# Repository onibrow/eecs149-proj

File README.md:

# EECS149/249A Final Project - Bop It! Rhythm Game

Sanga Park, Seiya Ono, Ryan Tsang, Jehan Yang

[Video](https://www.youtube.com/watch?v=G22i39vs388&feature=youtu.be)

------
Setting up a lab computer:

```bash
cd ~/buckler/software
git clone https://github.com/onibrow/eecs149-proj
cd eecs149-proj
./setup_vm
```

## Proposal (10/25)

[Spreadsheet](https://docs.google.com/spreadsheets/d/1WutyDuHFwCbV_97uEuxx-2Y0jQ0Z9K7RMsq6U2ZCgrc/edit?usp=sharing)

**Project Goal**

We will implement a discrete note, single dimension rhythm game similar to Guitar Hero where the player is required to, on beat, actuate inputs from a pool of predefined discrete buttons. We will take this style of gameplay and translate into a Bop It driven hardware and LED display for the beat map.

**Project Approach**

The gameplay with be modeled as a state machine that keeps track of the state of the game (in game play, idling, song selection, etc). The sensor inputs will generate interrupts that trigger different events within the game. Timing and synchronicity will be very important to make sure the LEDs are lighting up on cue with the music. As a final product, we would like to seamlessly take input from the player and translate that to well timed gameplay with LED signals and music.

## Getting out of dependency hell

1. Try to compile. What library is it missing? ex: `blah.h`
1. Does the file exist in the sdk? Find it by going to the sdk folder `~/buckler/software/nrf52x-base/sdk/nrf5_sdk_15.3.0` and running `find . -name 'blah.*'`. Take note of the directory the header and C file are located in.
1. Edit `eecs149-proj/vm_setup/Includes.mk`. You will need to add **2 Lines**:
    1. Near line 180, the `SDK_HEADER_PATHS` should end and become `SDK_SOURCE_PATHS`. Add a new line at the end of the header paths and add the directory you found in step 2 for the header file. You might want to check if that directory is being checked already. ex: `SDK_HEADER_PATHS += $(SDK_ROOT)external/components/`
    1. Near line 270, the `SDK_SOURCE_PATHS` should end and is followed by `ifdef SERIALIZATiON_MODE`. Add a new line at the end of the source paths and add the directory you found in step 2 for the C file. Similarly, you might want to check if that directory is already being sourced. ex: `SDK_SOURCE_PATHS += $(SDK_ROOT)external/components/`
1. Edit `eecs149-proj/vm_setup/Board.mk`. You will need to add **1 Line**:
    1. Near line 95, the list of `BOARD_SOURCES` should end. Add the C file at the end of the list (make sure to terminate with a `\`). ex: `blah.c\`
1. Repeat the above steps for all dependencies.

## Notes
Meeting
MP3 files are compressed so they need to be decoded to be played on a DAC -> this isn't particularly ideal so we will switch over to WAV files which are uncompressed. From Audacity, we can see that we can save them in various formats (16 bit or 24 bit PCM), which will allow us to basically read in binary and shove them into either the I2S registers or over I2C. [Here](https://www.sparkfun.com/tutorials/160)'s a tutorial on how to play WAV files and goes over their limitations. 

## Useful Links:

[nRF52 Product Spec](https://infocenter.nordicsemi.com/pdf/nRF52832_PS_v1.4.pdf)

* I2S begins page 445
* [Loopback example for sanity check](https://infocenter.nordicsemi.com/index.jsp?topic=%2Fcom.nordic.infocenter.sdk5.v15.2.0%2Fi2s_example_loopback.html&cp=4_0_0_4_5_14)
* [nRF SDK I2S](https://infocenter.nordicsemi.com/topic/com.nordic.infocenter.sdk5.v15.3.0/group__nrfx__i2s.html)
* [MCP4725 DAC Driver](https://infocenter.nordicsemi.com/topic/com.nordic.infocenter.sdk5.v15.3.0/group__mcp4725.html)

[Nordic SD Card](https://infocenter.nordicsemi.com/topic/com.nordic.infocenter.sdk5.v15.3.0/app_sdcard_example.html)

[Nordic Timers](https://infocenter.nordicsemi.com/index.jsp?topic=%2Fcom.nordic.infocenter.sdk5.v15.3.0%2Fgroup__app__timer.html)

[SparkFun's Intro to SPI](https://learn.sparkfun.com/tutorials/serial-peripheral-interface-spi/all)

[RPi WS2801 SPI Interface](https://tutorials-raspberrypi.com/how-to-control-a-raspberry-pi-ws2801-rgb-led-strip/)

[WS2801 Datasheet](https://cdn-shop.adafruit.com/datasheets/WS2801.pdf)

[Adafruit WS2801 RPi SPI Library](https://github.com/adafruit/Adafruit_CircuitPython_WS2801)

[Audio Python Syncing](https://github.com/scottlawsonbc/audio-reactive-led-strip)

[RPI GPIO Interrupt Handling](http://raspberrywebserver.com/gpio/using-interrupt-driven-gpio.html)

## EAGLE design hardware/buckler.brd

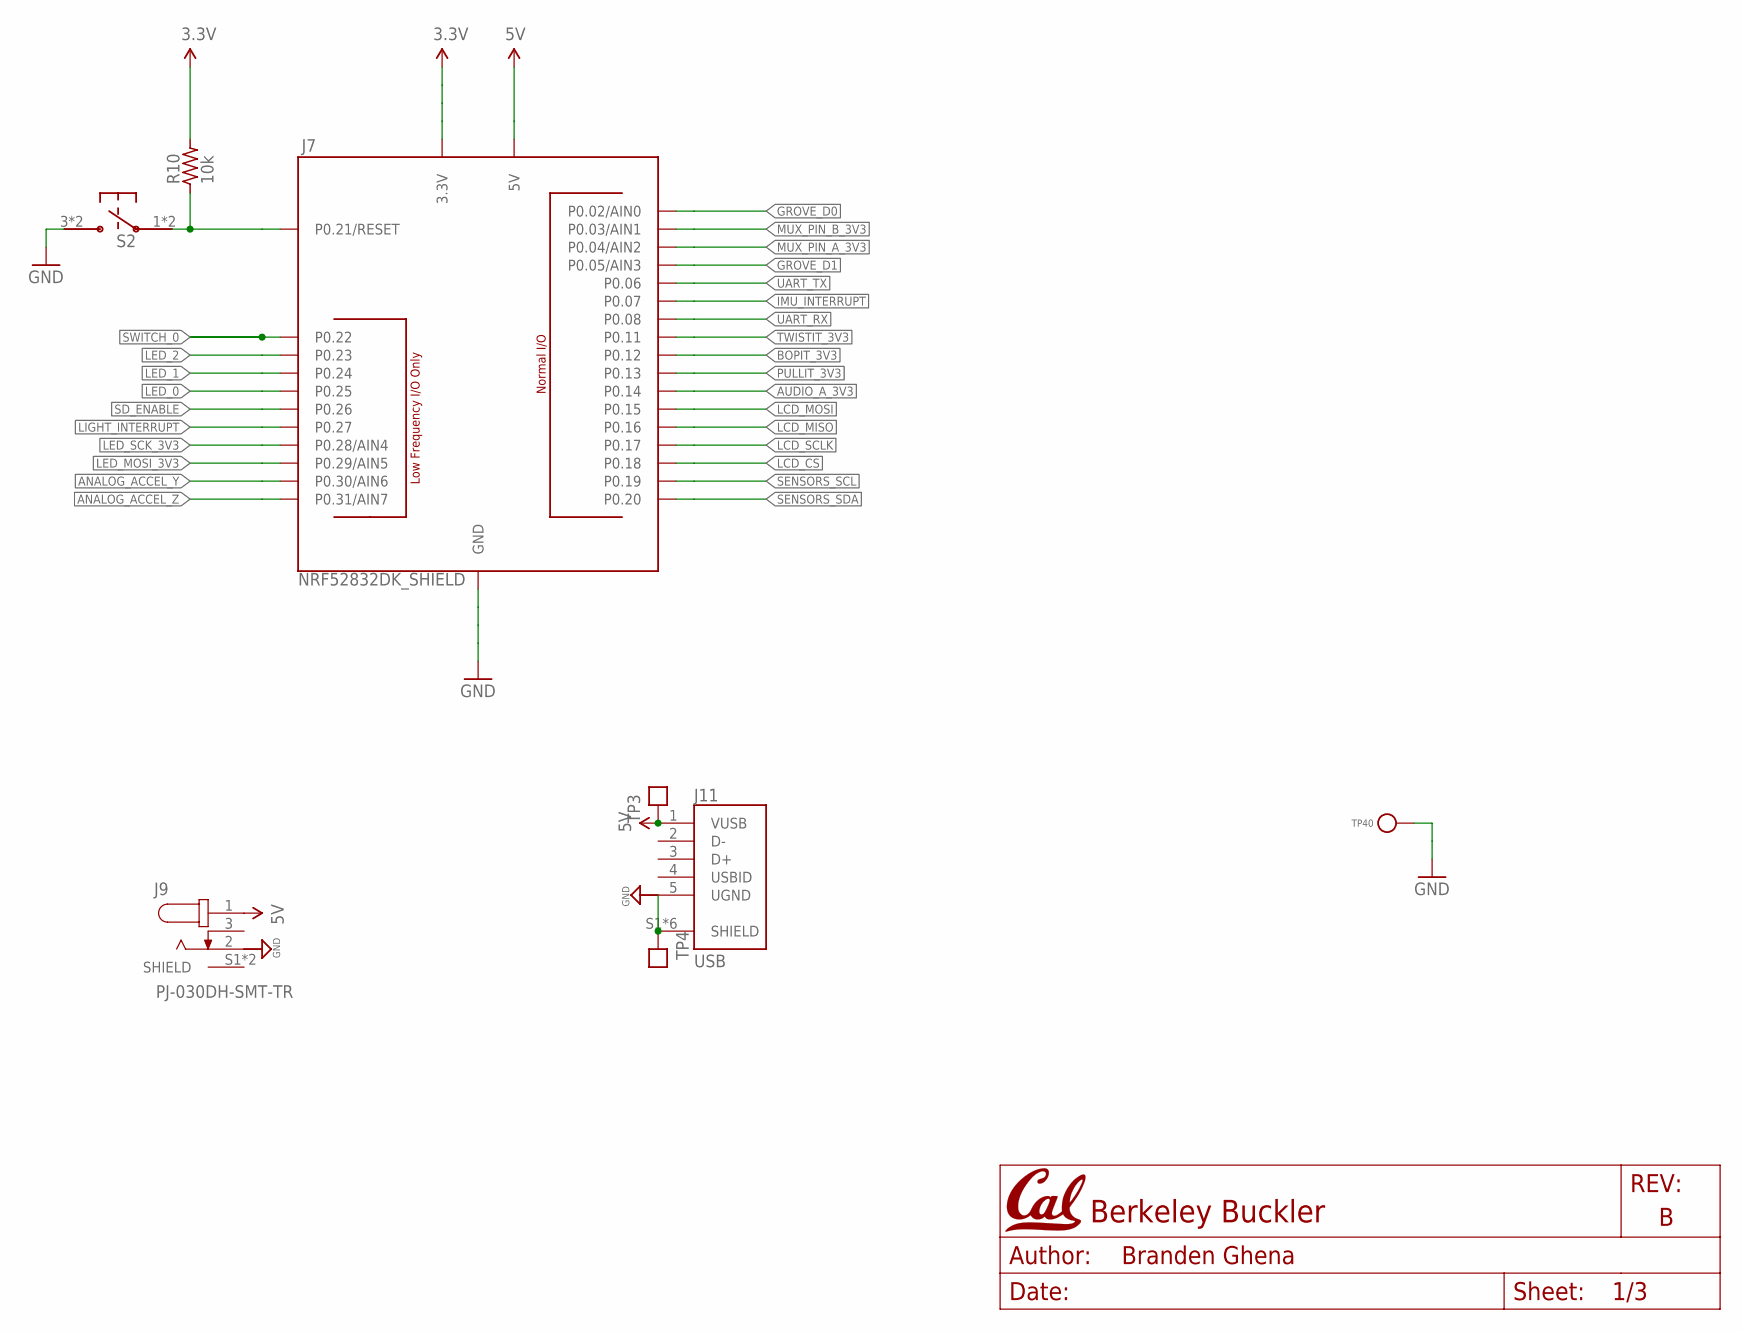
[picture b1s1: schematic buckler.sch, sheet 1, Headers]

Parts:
J7: NRF52832DK_SHIELD; DIGIKEY1 S1011EC-10-ND
J9: PJ-030DH-SMT-TR; CUI_PJ-030DH-SMT-TR
J11: USB; FCI_10103594-0001LF
R10: 10k; 0603-RES; MPN RC1005F103CS; DIGIKEY 1276-3431-1-ND
S2: PTS645SM43SMTR92; PTS645; MPN PTS645SM43SMTR92 LFS
TP3, TP4: TEST_POINTTHRU; TEST_POINT
TP40: TEST_POINT_0.078IN; TESTPOINT_0.078IN; MPN 1520-2; DIGIKEY 36-1520-2-ND

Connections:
3.3V: J7.3.3V@0 (3.3V), J7.3.3V@1 (3.3V), J7.3.3V@2 (3.3V), R10.2; also elsewhere on the board
5V: J7.5V, J9.1, J11.1 (VUSB), TP3.1; also elsewhere on the board
!IMU_INTERRUPT: J7.P0.07
!LCD_CS: J7.P0.18; also elsewhere on the board
!LED_0: J7.P0.25; also elsewhere on the board
!LED_1: J7.P0.24; also elsewhere on the board
!LED_2: J7.P0.23; also elsewhere on the board
!LIGHT_INTERRUPT: J7.P0.27
!RESET: J7.P0.21 (P0.21/RESET), R10.1, S2.1, S2.2
ANALOG_ACCEL_Y: J7.P0.30 (P0.30/AIN6)
ANALOG_ACCEL_Z: J7.P0.31 (P0.31/AIN7)
AUDIO_A_3V3: J7.P0.14; also elsewhere on the board
BOPIT_3V3: J7.P0.12; also elsewhere on the board
GND: J7.GND@0 (GND), J7.GND@1 (GND), J7.GND@2 (GND), J9.2, J11.5 (UGND), J11.S1 (SHIELD), J11.S2 (SHIELD), J11.S3 (SHIELD), J11.S4 (SHIELD), J11.S5 (SHIELD), J11.S6 (SHIELD), S2.3, S2.4, TP4.1, TP40.1; also elsewhere on the board
GROVE_D0: J7.P0.02 (P0.02/AIN0)
GROVE_D1: J7.P0.05 (P0.05/AIN3)
LCD_MISO: J7.P0.16; also elsewhere on the board
LCD_MOSI: J7.P0.15; also elsewhere on the board
LCD_SCLK: J7.P0.17; also elsewhere on the board
LED_MOSI_3V3: J7.P0.29 (P0.29/AIN5); also elsewhere on the board
LED_SCK_3V3: J7.P0.28 (P0.28/AIN4); also elsewhere on the board
MUX_PIN_A_3V3: J7.P0.04 (P0.04/AIN2); also elsewhere on the board
MUX_PIN_B_3V3: J7.P0.03 (P0.03/AIN1); also elsewhere on the board
PULLIT_3V3: J7.P0.13; also elsewhere on the board
SD_ENABLE: J7.P0.26
SENSORS_SCL: J7.P0.19
SENSORS_SDA: J7.P0.20
SWITCH_0: J7.P0.22
TWISTIT_3V3: J7.P0.11; also elsewhere on the board
UART_RX: J7.P0.08
UART_TX: J7.P0.06

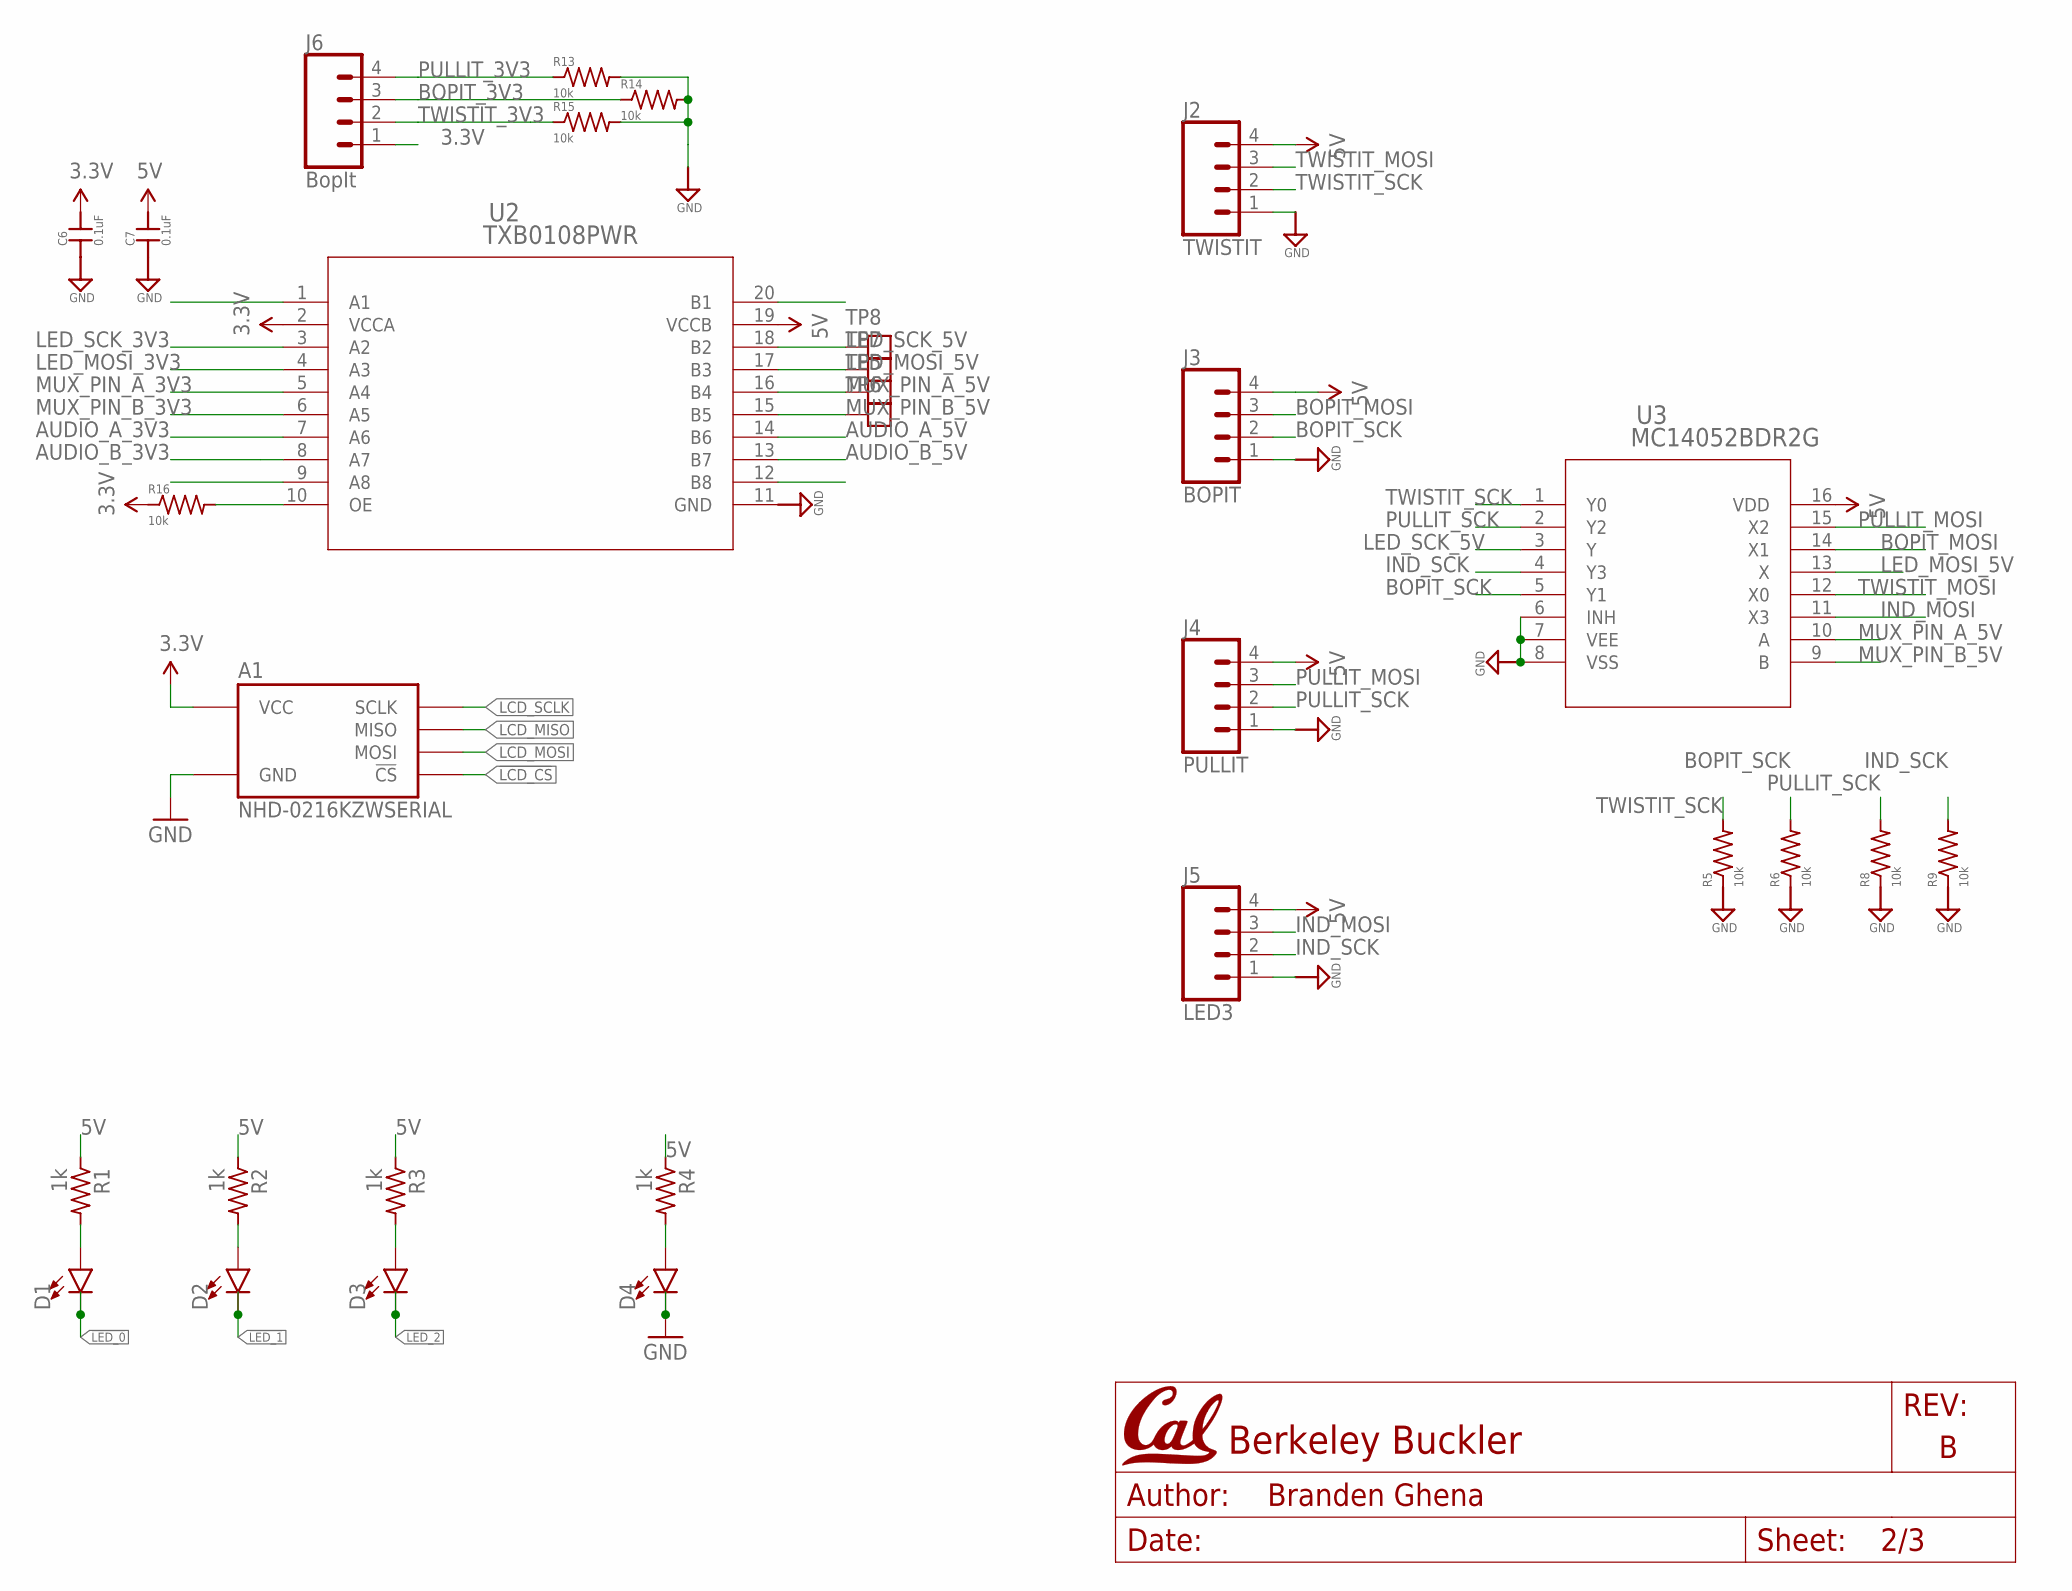
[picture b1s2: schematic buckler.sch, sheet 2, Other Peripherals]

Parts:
A1: NHD-0216KZWSERIAL; NHD-0216KZW; DIGIKEY1 NHD-0216KZW-AG5-ND
C6, C7: 0.1uF; 0603-CAP
D1, D2, D3, D4: LED0603; LED-0603
J2: TWISTIT; MOLEX-1X4
J3: BOPIT; MOLEX-1X4
J4: PULLIT; MOLEX-1X4
J5: LED3; MOLEX-1X4
J6: BopIt; MOLEX-1X4
R1, R2, R3, R4: 1k; 0603-RES; MPN RMCF0402FT1K00; DIGIKEY RMCF0402FT1K00CT-ND
R5, R6, R8, R9, R13, R14, R15, R16: 10k; 0603-RES
TP5, TP6, TP7, TP8: TEST_POINTTHRU; TEST_POINT
U2: TXB0108PWR; PW20
U3: MC14052BDR2G; SOIC-16

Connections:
3.3V: A1.2 (VCC), C6.2, J6.1, R16.1, U2.2 (VCCA); also elsewhere on the board
5V: C7.2, J2.4, J3.4, J4.4, J5.4, R1.1, R2.1, R3.1, R4.1, U2.19 (VCCB), U3.16 (VDD); also elsewhere on the board
!LCD_CS: A1.16 (!CS); also elsewhere on the board
!LED_0: D1.C; also elsewhere on the board
!LED_1: D2.C; also elsewhere on the board
!LED_2: D3.C; also elsewhere on the board
AUDIO_A_3V3: U2.7 (A6); also elsewhere on the board
AUDIO_A_5V: U2.14 (B6); also elsewhere on the board
AUDIO_B_3V3: U2.8 (A7)
AUDIO_B_5V: U2.13 (B7); also elsewhere on the board
BOPIT_3V3: J6.3, R14.1; also elsewhere on the board
BOPIT_MOSI: J3.3, U3.14 (X1)
BOPIT_SCK: J3.2, R6.2, U3.5 (Y1)
GND: A1.1 (GND), C6.1, C7.1, D4.C, J2.1, J3.1, J4.1, J5.1, R5.1, R6.1, R8.1, R9.1, R13.2, R14.2, R15.2, U2.11 (GND), U3.6 (INH), U3.7 (VEE), U3.8 (VSS); also elsewhere on the board
IND_MOSI: J5.3, U3.11 (X3)
IND_SCK: J5.2, R9.2, U3.4 (Y3)
LCD_MISO: A1.13 (MISO); also elsewhere on the board
LCD_MOSI: A1.14 (MOSI); also elsewhere on the board
LCD_SCLK: A1.12 (SCLK); also elsewhere on the board
LED_MOSI_3V3: U2.4 (A3); also elsewhere on the board
LED_MOSI_5V: TP7.1, U2.17 (B3), U3.13 (X)
LED_SCK_3V3: U2.3 (A2); also elsewhere on the board
LED_SCK_5V: TP8.1, U2.18 (B2), U3.3 (Y)
MUX_PIN_A_3V3: U2.5 (A4); also elsewhere on the board
MUX_PIN_A_5V: TP5.1, U2.16 (B4), U3.10 (A)
MUX_PIN_B_3V3: U2.6 (A5); also elsewhere on the board
MUX_PIN_B_5V: TP6.1, U2.15 (B5), U3.9 (B)
unnamed: R16.2, U2.10 (OE)
unnamed: D4.A, R4.2
unnamed: D3.A, R3.2
unnamed: D2.A, R2.2
unnamed: D1.A, R1.2
PULLIT_3V3: J6.4, R13.1; also elsewhere on the board
PULLIT_MOSI: J4.3, U3.15 (X2)
PULLIT_SCK: J4.2, R8.2, U3.2 (Y2)
TWISTIT_3V3: J6.2, R15.1; also elsewhere on the board
TWISTIT_MOSI: J2.3, U3.12 (X0)
TWISTIT_SCK: J2.2, R5.2, U3.1 (Y0)

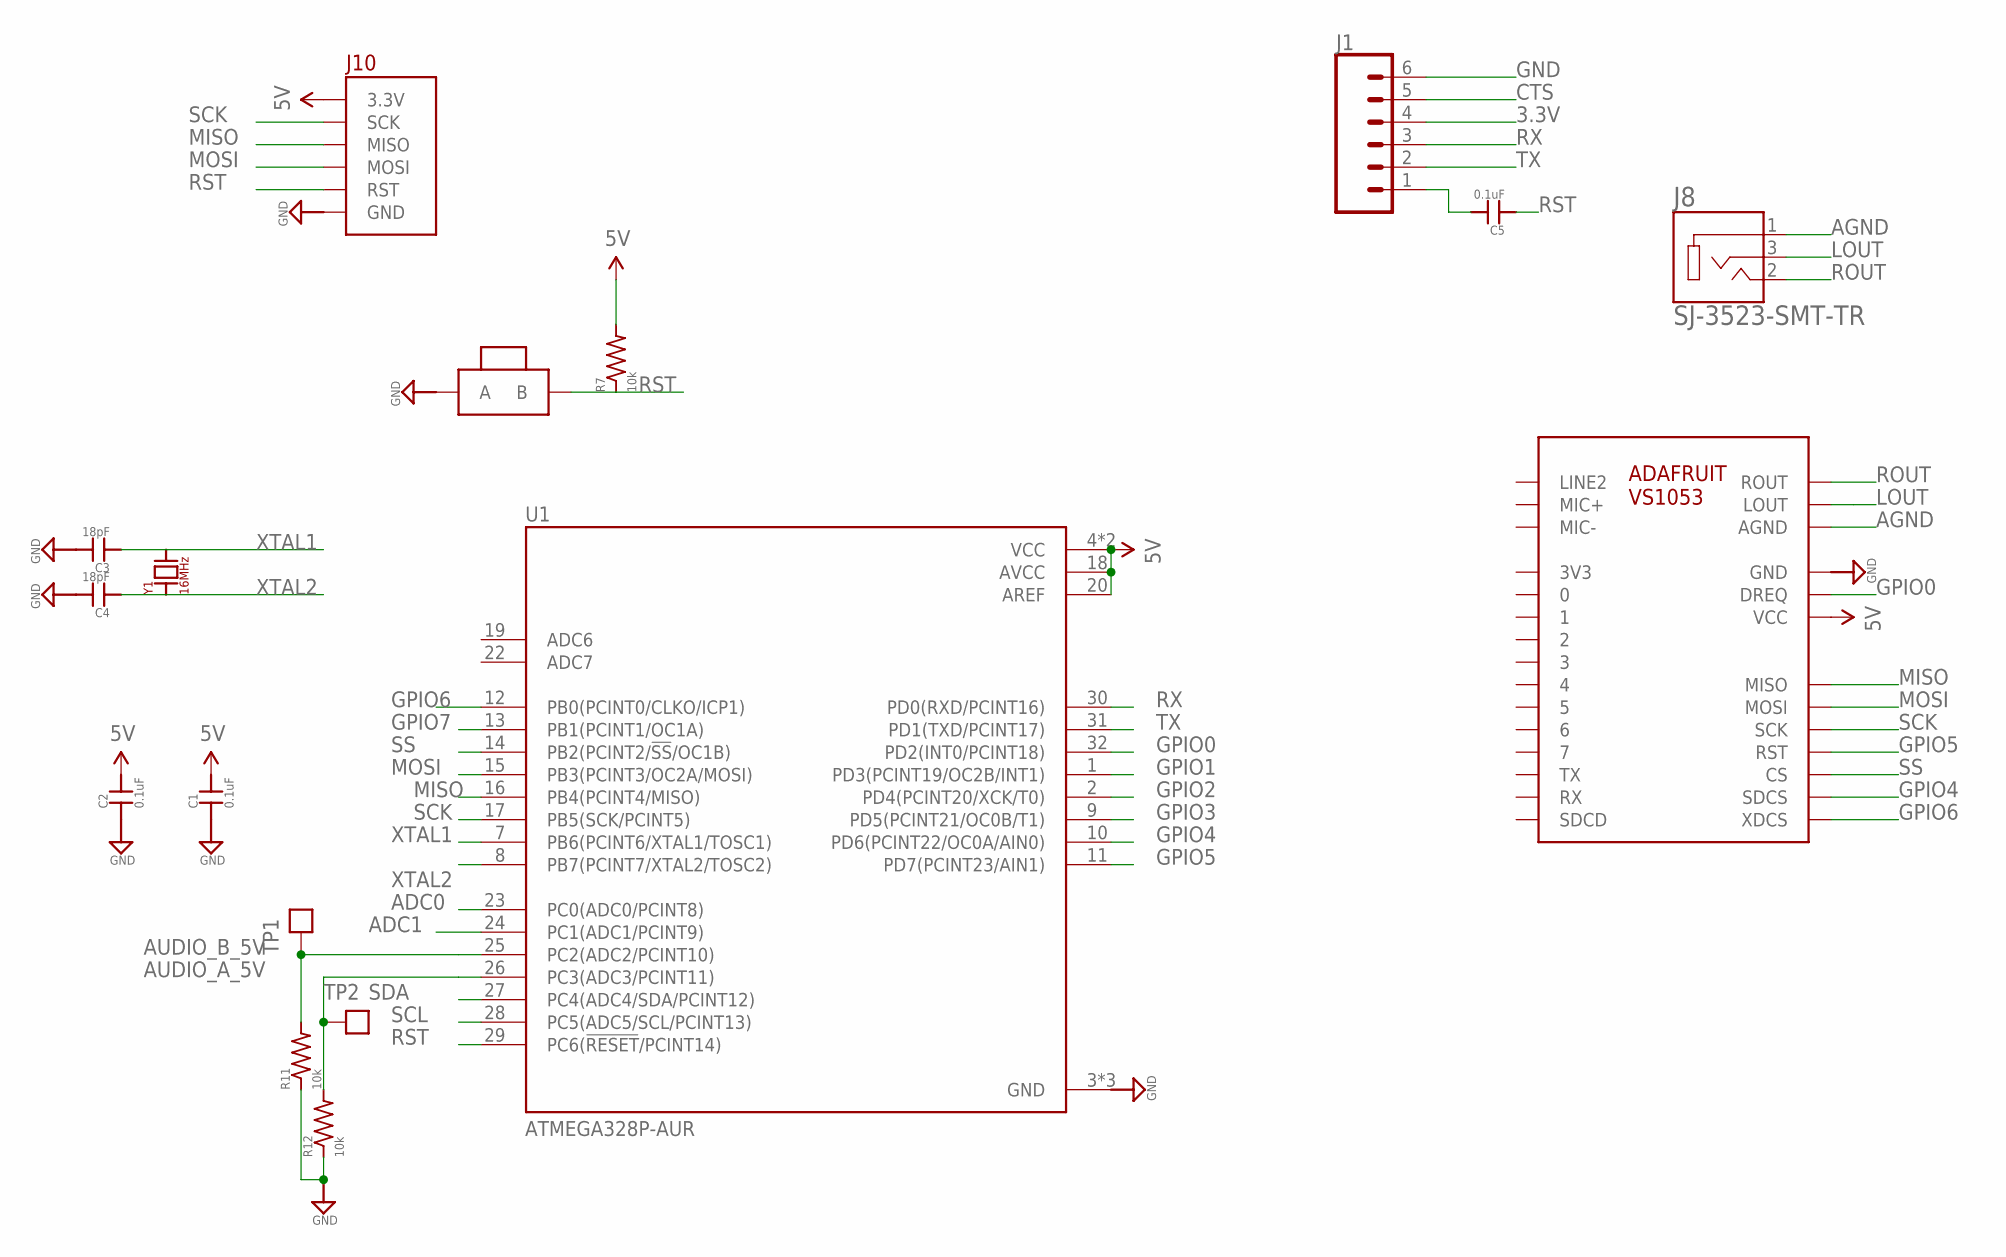
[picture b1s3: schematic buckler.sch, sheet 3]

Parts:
C1, C2, C5: 0.1uF; 0603-CAP
C3, C4: 18pF; 0603-CAP
J1: CONN_06NO_SILK_FEMALE_PTH; 1X06_NO_SILK
J8: SJ-3523-SMT-TR; CUI_SJ-3523-SMT-TR
J10: BURNIN
R7: 10k; R0603
R11, R12: 10k; 0603-RES
SW1: BTN-PTS810; BTN_PTS810
TP1, TP2: TEST_POINTTHRU; TEST_POINT
U1: ATMEGA328P-AUR; QFP80P900X900X120-32N
U4: ADAFRUIT_VS1053
Y1: 16MHz; XTAL500X320X130N

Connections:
3.3V: J1.4; also elsewhere on the board
5V: C1.2, C2.2, J10.3.3V, R7.2, U1.4 (VCC), U1.6 (VCC), U1.18 (AVCC), U1.20 (AREF), U4.26 (VCC); also elsewhere on the board
ADC0: U1.23 (PC0(ADC0/PCINT8))
ADC1: U1.24 (PC1(ADC1/PCINT9))
AGND: J8.1, U4.4 (AGND), U4.29 (AGND), U4.30 (AGND)
AUDIO_A_5V: R12.2, TP2.1, U1.26 (PC3(ADC3/PCINT11)); also elsewhere on the board
AUDIO_B_5V: R11.2, TP1.1, U1.25 (PC2(ADC2/PCINT10)); also elsewhere on the board
CTS: J1.5
GND: C1.1, C2.1, C3.2, C4.2, J1.6, J10.GND, R11.1, R12.1, SW1.1 (A), SW1.2 (A), U1.3 (GND), U1.5 (GND), U1.21 (GND), U4.24 (GND), U4.28 (GND); also elsewhere on the board
GPIO0: U1.32 (PD2(INT0/PCINT18)), U4.27 (DREQ)
GPIO1: U1.1 (PD3(PCINT19/OC2B/INT1))
GPIO2: U1.2 (PD4(PCINT20/XCK/T0))
GPIO3: U1.9 (PD5(PCINT21/OC0B/T1))
GPIO4: U1.10 (PD6(PCINT22/OC0A/AIN0)), U4.18 (SDCS)
GPIO5: U1.11 (PD7(PCINT23/AIN1)), U4.20 (RST)
GPIO6: U1.12 (PB0(PCINT0/CLKO/ICP1)), U4.17 (XDCS)
GPIO7: U1.13 (PB1(PCINT1/OC1A))
LOUT: J8.3, U4.31 (LOUT)
MISO: J10.MISO, U1.16 (PB4(PCINT4/MISO)), U4.23 (MISO)
MOSI: J10.MOSI, U1.15 (PB3(PCINT3/OC2A/MOSI)), U4.22 (MOSI)
unnamed: C5.2, J1.1
ROUT: J8.2, U4.32 (ROUT)
RST: C5.1, J10.RST, R7.1, SW1.3 (B), SW1.4 (B), U1.29 (PC6(!RESET!/PCINT14))
RX: J1.3, U1.30 (PD0(RXD/PCINT16))
SCK: J10.SCK, U1.17 (PB5(SCK/PCINT5)), U4.21 (SCK)
SCL: U1.28 (PC5(ADC5/SCL/PCINT13))
SDA: U1.27 (PC4(ADC4/SDA/PCINT12))
SS: U1.14 (PB2(PCINT2/!SS!/OC1B)), U4.19 (CS)
TX: J1.2, U1.31 (PD1(TXD/PCINT17))
XTAL1: C3.1, U1.7 (PB6(PCINT6/XTAL1/TOSC1)), Y1.2 (B)
XTAL2: C4.1, U1.8 (PB7(PCINT7/XTAL2/TOSC2)), Y1.1 (A)

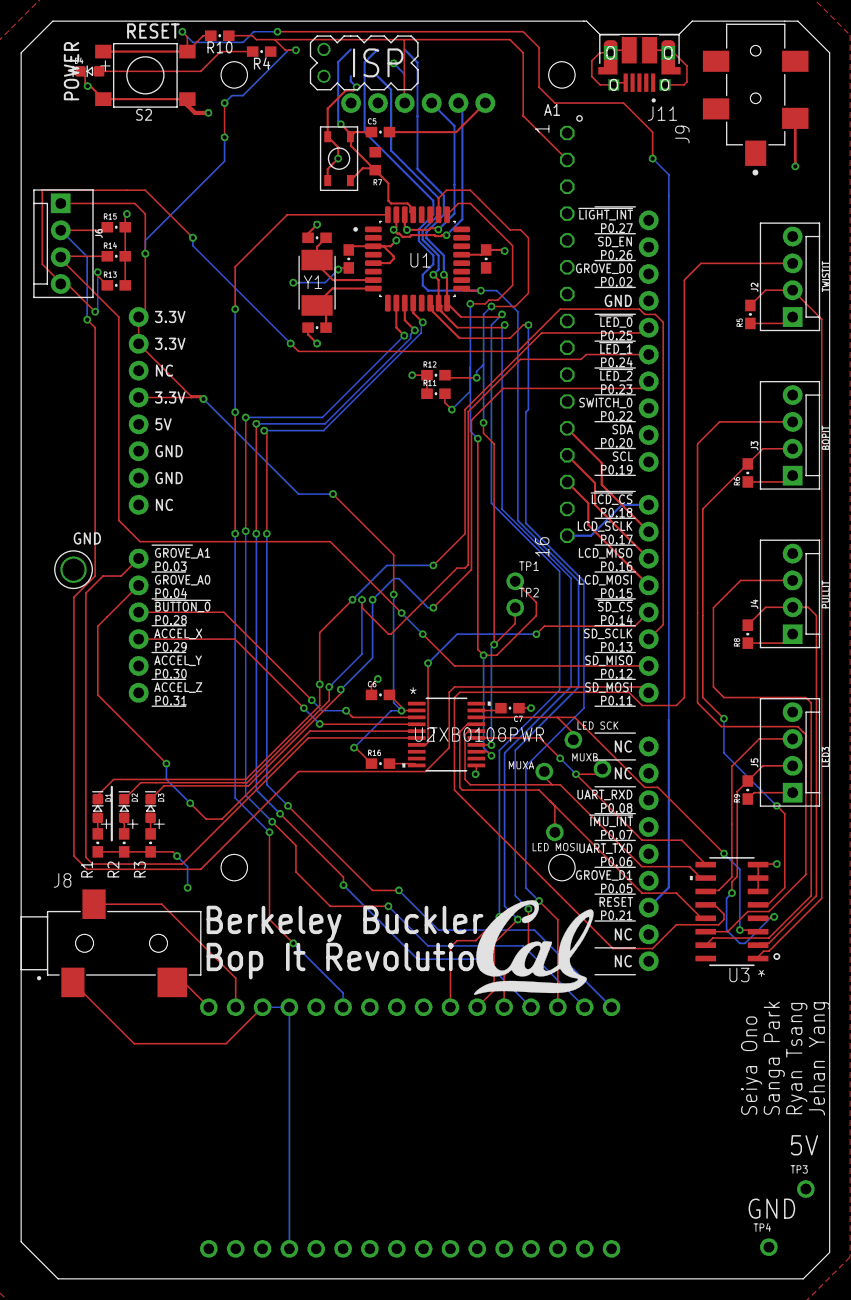
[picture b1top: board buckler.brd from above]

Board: 2 copper layers, 76.5 x 119.0 mm, 56 parts (0 on the bottom side), 55 nets.

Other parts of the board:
U$5: UCB_CAL_350MIL

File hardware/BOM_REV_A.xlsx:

Comment | Designator | Footprint | LCSC Part #（optional）
0.1uF | C1, C2, C5, C6, C7 | 0603_C | C14663
18pF | C3, C4 | 0603_C | C1647
10k | R5, R6, R7, R8, R9, R10, R11, R12, R13, R14, R15, R16 | 0603_R | C25804
1k | R1, R2, R3, R4 | 0603_R | C21190
ATMEGA328P | U1 | QFN-44_EP_7x7x0.5P | C14877
Green | D1 | LED_0603 | C72043
Red | D2 | LED_0603 | C2286
Green | D3 | LED_0603 | C72043
Red | D4 | LED_0603 | C2286

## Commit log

2019-10-18 Initialize readme
2019-10-18 Add resources to readme
2019-10-18 Start proposal
2019-10-21 Add more useful links
2019-10-21 Add link to spreadsheet
2019-10-27 Move from depracated library
2019-10-28 Add test files for rpi buses and audio
2019-10-28 set audio to correct bpm, changed to 240 beats
2019-10-29 Add nrf product spec
2019-10-31 Update README.md
    Added WS2801 datasheet
2019-11-08 Add vm setup code
2019-11-08 Add voltage comands
2019-11-13 add example code for i2s
2019-11-14 get i2s and dac to work
2019-11-14 add test wav file
2019-11-14 add more setup for git
2019-11-14 Organize test audio files
2019-11-14 More work on i2s and sdcard
2019-11-14 clean up build files
2019-11-14 Fix board mk
2019-11-18 Add nordic sd card
2019-11-18 Add includes file and fix sd card pins
2019-11-18 Add timer
2019-11-18 game loop for lcd
2019-11-19 Dependency Hell
2019-11-19 Fix formatting
2019-11-19 More sd card progress
2019-11-19 start i2s audio testing
2019-11-19 Add lcd documentation
2019-11-19 add more config parameters
2019-11-20 resolved wrong directory - not compiling issue for SD Card
2019-11-20 SD card now reads, but buffer offset issue exists
2019-11-20 SD card now reads, but buffer offset issue exists, also TWI disabled
2019-11-21 Get sd card reads to work
2019-11-21 Added LEDCode Folder with all relevent LED/SPI files
2019-11-21 change copies to links
2019-11-21 start new thing to integrate lcd and sd
2019-11-26 working on merging sd card and lcd
2019-12-03 sd card and bpm work simultaneously
2019-12-04 bop it input works
2019-12-04 last commit on sangas branch
2019-12-05 fix sd card merge conflict
2019-12-05 README.md updated to reflect folder
2019-12-05 final cleaning
2019-12-05 This actuallyworks now
2019-12-05 Add setup code
2019-12-05 Get i2s working!!
2019-12-05 fix sd card conflict
2019-12-05 Clean up audio files
2019-12-05 clean up code a bit ad fix lsb msb nonsense
2019-12-05 Removed unnecessary linked_list files
2019-12-05 API in Progress
2019-12-05 Still using linked list implementation, mux now working (2 strips)
2019-12-05 API tested and fixed.
2019-12-05 start reading wav files and implement new i2s handler
2019-12-05 LED API Works, lightly tested, have not checked for memory leaks
2019-12-05 Added macro for mux pins A and B
2019-12-05 Rewrote API that doesn't use linked list and added MUX support. Untested
2019-12-05 Read file and play music at the same time
2019-12-05 more wav file work
2019-12-05 update audio files
2019-12-05 remove long sons
2019-12-05 Forgot to initialize gpio pins for mux. fixed and compiles. still untested.
2019-12-05 3rd LED Strip Added, colors picked, pull down resistors added
2019-12-05 Added a debugging function: printState()
2019-12-05 cleaned up
2019-12-05 integration of led and bpm
2019-12-05 integration
2019-12-05 Turned show() into a bool, returns true if the oldest sent light was on
2019-12-05 more progress on led speed
2019-12-06 sugar beatmap written in txt file, can copy it to main.c file
2019-12-06 lights synchronized with music now
2019-12-06 git is for transfering files.
2019-12-06 git is for transfering files
2019-12-06 works
2019-12-06 changed beatmap to be a uint8_t array instead of 2d car array for space
2019-12-07 Game can now be replayed after ending
2019-12-12 Finish the board
2019-12-12 added song selection
2019-12-13 multiple song selection
2019-12-13 What Ive Done and Derezzed added and sync'd. minor bugs
2019-12-17 add the audio player files
2019-12-17 fix timings of songs and add loading screen
2019-12-18 rename final picture
2019-12-19 Last commit of the Project (added green light on hit)

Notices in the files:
parts and their libraries:
COPYRIGHT: Copyright (C) 2016 Accelerated Designs. All rights reserved
